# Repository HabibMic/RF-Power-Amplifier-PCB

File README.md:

# RF Power Amplifier & Impedance Matching System

## Overview
This repository contains the design and 4-layer PCB layout for a high-frequency RF power amplifier. The system features an active gain stage and two separate impedance matching networks designed to interface a non-standard "test load" with a 50 Ohm system.

## Design Specifications

### 1. Active RF Gain Block
* **Amplifier**: Based on the Mini-Circuits GALI-S66 integrated circuit.
* **Biasing**: Utilizes a 9V DC supply with a 300 Ohm total bias resistance (implemented as two 150 Ohm resistors in series) to set stable operating current.
* **RF Isolation**: Employs a Ferrite Bead (FB1) as an RF choke to isolate the DC path from high-frequency signals.
* **Coupling & Decoupling**: Includes 100pF DC-blocking capacitors at the input and output ports, and a decoupling array (10nF and 100uF) to filter power supply ripple.

### 2. Impedance Matching Networks
* **Short-Circuit Shunt Stub**: Calculated via Smith Chart analysis for a physical distance of 86.3 and a stub length of 10.7 mm.
* **Quarter-Wave Transformer**: A lambda/4 transmission line section with a calculated characteristic impedance of 70.7 Ohms.

## PCB Manufacturing
* **Form Factor**: 48.26 mm x 48.26 mm, compliant with 5 cm x 5 cm laboratory constraints.
* **Stackup**: JLC04161H-7628 4-layer standard configuration.
* **Layer Strategy**: 
    * **Top Layer**: Signal routing and RF microstrip lines.
    * **Internal Layer 1**: Dedicated ground plane for impedance control.
    * **Internal Layer 2**: Power plane.
* **Thermal Management**: Via-stitching array implemented under the GALI-S66 thermal pad for heat transfer to internal planes.

## Lab Characterization
Testing was performed using a Keysight N9912A FieldFox Vector Network Analyzer.
* **Measurement**: S-parameter characterization (S11, S21) across a 50 to 150 MHz sweep.
* **Calibration**: Applied port extension techniques to null out phase delays from coaxial test cables.

---
**Author**: Micheal Habib

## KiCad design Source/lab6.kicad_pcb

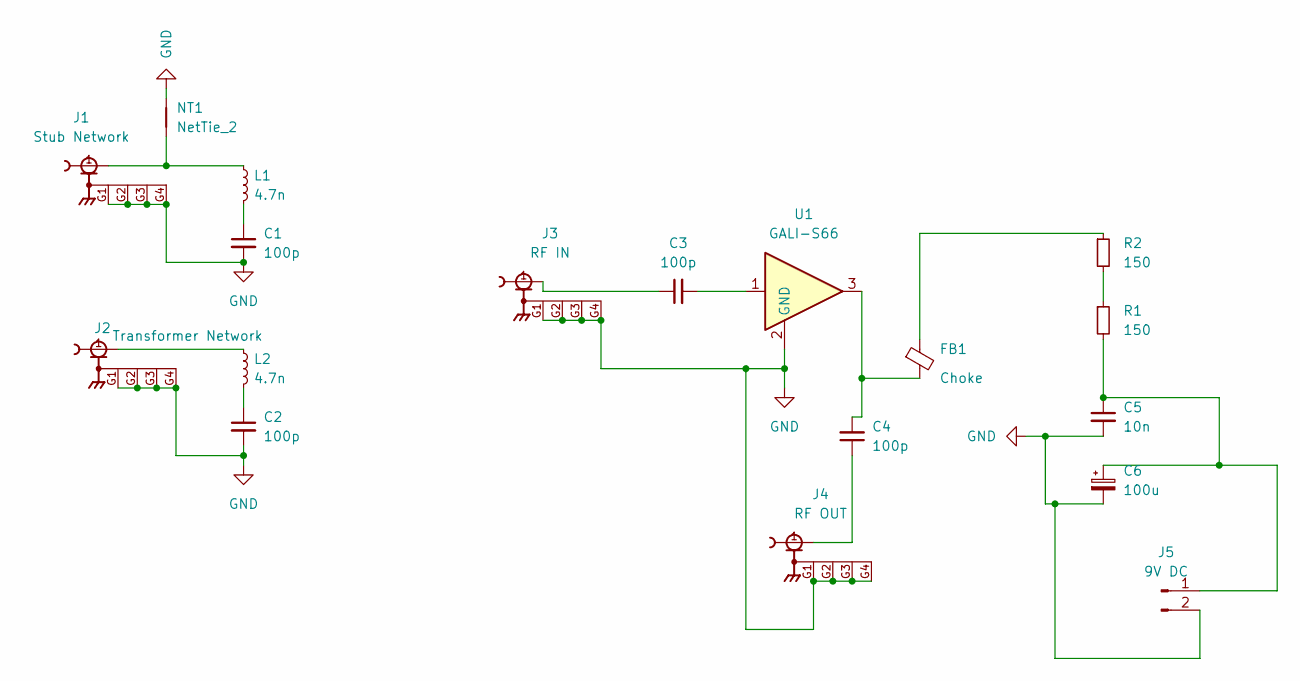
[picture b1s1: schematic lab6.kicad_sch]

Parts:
C1, C2: 100p; C_1206_3216Metric
C3, C4: 100p; C_0805_2012Metric
C5: 10n; C_0805_2012Metric
C6: 100u; CP_Elec_6.3x5.4_Nichicon
FB1: Choke; L_0805_2012Metric
J1: Stub Network; RFPC-SMA28-F; PARTREV 1.0
J2: Transformer Network; RFPC-SMA28-F; PARTREV 1.0
J3: RF IN; RFPC-SMA28-F; PARTREV 1.0
J4: RF OUT; RFPC-SMA28-F; PARTREV 1.0
J5: 9V DC; PinHeader_1x02_P2.54mm_Vertical
L1, L2: 4.7n; L_1008_2520Metric
NT1: NetTie_2; NetTie-2_SMD_Pad0.5mm
R1, R2: 150; R_MiniMELF_MMA-0204
U1: GALI-S66

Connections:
GND: C1.2, C2.2, C5.2, C6.2, J1.G1, J1.G2, J1.G3, J1.G4, J2.G1, J2.G2, J2.G3, J2.G4, J3.G1, J3.G2, J3.G3, J3.G4, J4.G1, J4.G2, J4.G3, J4.G4, J5.2, NT1.1, U1.2 (GND)
unnamed: C1.1, L1.2
unnamed: C2.1, L2.2
unnamed: C3.1, J3.1
unnamed: C3.2, U1.1
unnamed: C4.1, J4.1
unnamed: C4.2, FB1.2, U1.3
unnamed: FB1.1, R2.1
unnamed: J1.1, L1.1, NT1.2
unnamed: J2.1, L2.1
unnamed: C5.1, C6.1, J5.1, R1.2
unnamed: R1.1, R2.2

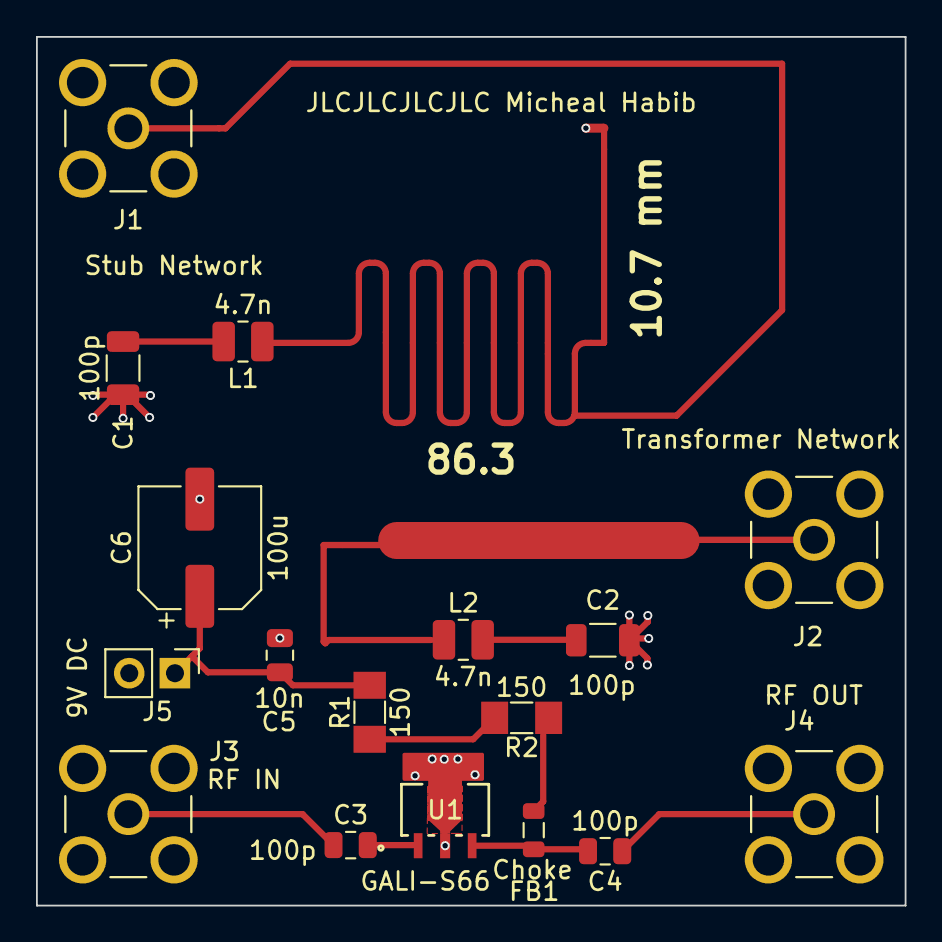
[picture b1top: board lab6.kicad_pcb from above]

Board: 4 copper layers, 48.3 x 48.3 mm, 18 parts (0 on the bottom side), 12 nets.
